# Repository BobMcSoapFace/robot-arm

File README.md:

# robot-arm

robot-arm is a 4-axis robot arm designed with modularity in mind. Depending on the maximum torque output of the motors and maximum range of the I2C wires, this project can support numerous limbs with only minor changes in code. Currently, the code is fixed to allowing two limbs and a hand on the robot.

I built this project mostly to challenge myself to tackle more complicated electronic and mechanical designs, but also because most hobbyist robot arms focus on using claws or grippers to pick up objects. For this project, the minor change of a claw to a hand that can sense its own orientation as well as high gear ratios allows for supporting heavier objects such as displays and light fixtures. 

All materials can be found within BOM.csv.
# Electronics
## Limb Controller PCB

## Main Controller PCB

# Setup Instructions
## Electronics
First solder the components onto each board based on the diagrams above. For this project only 1 of the main controller boards are required, however 5 limb controller boards are required as well (with 1 not requiring a corresponding stepper motor nor driver).

On the main controller board, use PlatformIO to flash the main controller board using the code in /code/MainController. Since the board runs on an ESP32, flashing using other tools is likely be supported. Do not connect the XT60 while simultaneously flashing.

On the limb controller boards, use PlatformIO to flash via USB-C. While USB-C is connected, hold down the BOOT0 button and press the NRST button to enter DFU mode. Adjust the two parameters listed in the program based on which gearBox the controller is intended to be used for. Then, flash the firmware in /code/LimbController. 

## Assembly
Unless specified otherwise, all screws mentioned in the steps below refer to M4 1.6cm long screws meant for M4x6x6 inserts.
### Step 1 - baseSunGear

| Object | Print Quantity |
| --- | --- |
| 1 | 1x1 |
| 2 | 1x1 |
\* The "xN" represents the total number of gearboxes that require this part (meaning that a 3x4 quantity will need to be printed 12 times total)
1. For every hole about 0.7cm in diameter in every printable part, insert a M4x6x6 heat set threaded insert. 
   * In this part, only 1 threaded insert is required (the attachment between part 1 and part 2)
2. Screw part 1 to part 2.
3. Repeat this process 3 more times, for a total baseSunGear quantity of 4.
### Step 2 - gearReducer

<ins>**Note: There is a baseSunGear supposed to be between parts 1 and 2 and the three gears, but is hidden for better clarity.**</ins>
| Object | Print Quantity |
| --- | --- |
| 1 | 1x4 |
| 2 | 1x4 |
| 3 | 1x4 |
| 4 | 1x4 |
| Gear (27 teeth) | 3x4 |
\* The "xN" represents the total number of gearboxes that require this part (meaning that a 3x4 quantity will need to be printed 12 times total)

1. For every hole about 0.7cm in diameter in every printable part, insert a M4x6x6 heat set threaded insert. 
2. Using a hammer or other means, press fit a 6907ZZ bearing into part 1.
3. For each of the three 27 tooth gears, press fit a 6805 bearing into its cavity.
4. With the smaller hole side facing upwards, place each of the 3 gears on the poles of part 1.
5. Press fit a 6907ZZ bearing into the center hole of part 2.
6. With the baseSunGear's circular side of its part 2, press fit the baseSunGear into the 6907ZZ bearing of part 1 (the baseSunGear protruding upwards and aligning its teeth with the three gears).
7. Press fit part 2's 6907ZZ bearing on the baseSunGear's part 1.
7. Screw part 2 to part 1.
8. Screw part 3 to part 2.
9. Screw part 4 to part 3.
10. Repeat this process 3 more times, for a total gearReducer quantity of 4.
### Step 3 - gearReducerOutput

| Object | Print Quantity |
| --- | --- |
| 1 | 1x4 |
| 2 | 1x4 |
| 3 | 1x4 |
| Gear (27 teeth) | 3x4 |
\* The "xN" represents the total number of gearboxes that require this part (meaning that a 3x4 quantity will need to be printed 12 times total)
1. For every hole about 0.7cm in diameter in every printable part, insert a M4x6x6 heat set threaded insert. 
2. Using a hammer or other means, press fit a 6907ZZ bearing into part 1.
3. For each of the three 27 tooth gears, press fit a 6805 bearing into its cavity.
4. With the smaller hole side facing upwards, place each of the 3 gears on the poles of part 1.
5. Press fit a 6907ZZ bearing into the center hole of part 2.
6. Screw part 2 to part 1.
7. Screw part 3 to part 2.
9. Repeat this process 3 more times, for a total gearReducerOutput quantity of 4.
### Step 4 - gearBox

<ins>**Note: There is a 6020 bearing supposed to be between parts 1 and 2, but is hidden for better clarity.**</ins>
| Object | Print Quantity |
| --- | --- |
| 1 | 1x4 |
| 2 | 1x4 |
| 3 | 1x4 |
| 4 | 1x4 |
| 5 | 1x4 |
| 6 | 2x4 |
| gearReducerOutput | 1x4 |
| gearReducer | 1x4 |
| baseSunGear | 1x4 |
| Nema17 Stepper Motor | 1x4 |

1. For every hole about 0.7cm in diameter in every printable part, insert a M4x6x6 heat set threaded insert. 
2. Screw the two part 6's together using the outer brackets.
3. Screw the joined part 6's to part 7.
4. Screw part 4 to part 7.
5. Screw part 5 to part 7, with the screw terminals being accessible from the provided holes.
6. Align the asymmetrical shaft of the Nema17 stepper motor to the gearReducer's baseSunGear corresponding hole of the same shape, attaching the two objects.
7. Lower the gearReducer with the Nema17 into the ring gears, with the Nema17 aligning with the cavity provided by part 4.
8. Once the Nema17 is inside the cavity, screw part 3 to part 4, blocking the Nema17 from falling through.
9. Unscrew part 4 from part 3 for the gearReducer, and unscrew parts 2 and 3 from gearReducerOutput's part 1.
10. Lower the gearReducerOutput into the ring gear, aligning the 27 teeth gears with the base gear in the middle.
11. Screw back part 4 to part 3 for the gearReducer
12. Press fit the gearReducer's part 4 with the 6907ZZ bearing of the deattached gearReducerOutput's part 2, then screw parts 2 and 3 back to gearReducerOutput's part 1.
13. Press fit a 6020 bearing onto the gearbox's part 1, then press fit the bearing onto the gearReducerOutput's output cylinder (marked part 2)
14. Repeat 3 more times, for a total of 4 gearboxes.
### Step 5 - limb

| Object | Print Quantity |
| --- | --- |
| 1 | 1x2 |
| 3 | 2x2 |
| 4 | 1x2 |
| 5 | 1x2 |
| 7 | 1x2 |
| 8 | 1x2 |
| 9 | 1x2 |
| 10 | 1x2 |
| 11 | 1x2 |
| 12 | 1x2 |
| 13 | 1x2 |
| 14 | 1x2 |
\*Note that parts 15 and 6 are the same parts as 14 and 5 respectively.
1. For every hole about 0.7cm in diameter in every printable part, insert a M4x6x6 heat set threaded insert. 
2. On a gearbox, screw part 8 to the side with the controller.
3. Press fit a 6020 bearing to part 7, then screw part 7 to part 8.
4. Press fit part 1 to the bearing.
5. On the side of the gearbox outputting rotation, screw part 11 to the gearbox's output.
6. Screw part 12 to part 11.
7. Screw part 13 to parts 12 and 2.
8. Screw the two part 3's to part 13.
9. Screw part 5 to the two part 3's.
10. Screw part 4 to the part 3 on the side of the gearbox's controller.
11. Screw part 14 to the part 3 on the side of the gearbox's output.
12. Screw parts 14 and 4 to a second gearbox.
13. Repeat the steps above for a second limb, using the newly attached gearbox as the base (used in steps 2 and 5).
### Step 6 - base

| Object | Print Quantity |
| --- | --- |
| 1 | 1x1 |
| 2 | 7x1 |
| 4 | 1x1 |
| 5 | 7x1 |
| 6 | 8x1 |
| 7 | 1x1 |
| 8 | 1x1 |
| 9 | 1x1 |

\*Note that parts 15 and 6 are the same parts as 14 and 5 respectively.
1. For every hole about 0.7cm in diameter in every printable part, insert a M4x6x6 heat set threaded insert.
2. Using the inserts indicated by the region labeled #3, screw in 7 part 2's, avoiding the area covered by the gearbox controller.
3. To increase arm stability during movement, insert a heavy filler (e.g sand or gravel) or other similar heavy objects in equal distribution among the part 2's.
4. Screw a part 5 to each of the part 2's (7 total).
5. Screw a main controller PCB to part 1
6. Screw part 1 to the gearbox, and then screw part 7 to part 1.
7. Screw 8 part 6's to connect each of the part 7's together. 
7. With a gearbox in the middle and output side facing upwards, screw part 4 to the gearbox using the three holes.
### Step 7 - hand

| Object | Print Quantity |
| --- | --- |
| 1 | 1x1 |
| 2 | 1x1 |
| 3 | 1x1 |

1. For every hole about 0.7cm in diameter in every printable part, insert a M4x6x6 heat set threaded insert.
2. Screw part 3 to the output of the last limb's gearbox output.
3. Press fit a 6020 bearing to the last limb's gearbox controller side on the attached part, then press fit part 1 into the bearing.
4. Screw parts 1 and 3 together with part 2.
5. Screw the limb controller (part 4) to part 2.
   * Note that on this controller, an A4988 motor driver is not required.
### Step 8 - Connecting Limbs to Base
1. Using the screw terminals on each board, connect wires from the main controller to the limb controller in the base on one side. On the other side of the limb controller's screw terminals, connect more wires to the next gearbox's limb controllers, repeating the process for each controller until the hand's controller is connected.
   * You may have to unscrew some parts connecting to the gearbox to be able to reach the screw terminals.
   * Low capacitance wires are preferred, ex. solid core
   * Each terminal in the screw terminals on the limb controller are connected directly to the parallel terminal on the other screw terminal; simply connect the same terminals with each other
2. Lower the side of the first limb's initial gearbox with the output side facing the base's part 4 side with two holes for screws.
3. Deattach the limb's part 11 from the gearbox and part 12, then secure the gearbox in the base's part 4 by screwing in the two holes. Reattach part 11 afterwards.
4. On the other side of the gearbox, secure the gearbox with the three screw holes on base 4.

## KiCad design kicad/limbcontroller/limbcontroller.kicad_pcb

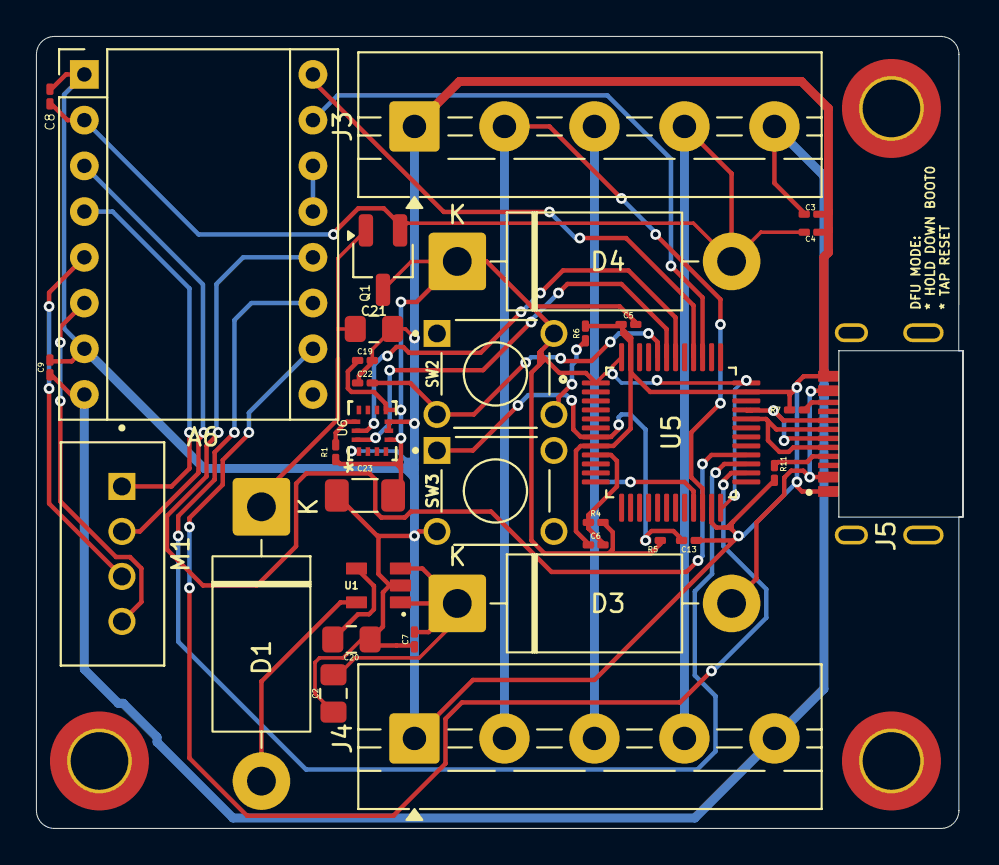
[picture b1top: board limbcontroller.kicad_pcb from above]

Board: 2 copper layers, 51.5 x 44.0 mm, 34 parts (0 on the bottom side), 32 nets.

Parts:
A6: Pololu_Breakout_A4988; Pololu_Breakout-16_15.2x20.3mm
C2, C21: 1uF; C_0805_2012Metric_Pad1.18x1.45mm_HandSolder
C3, C4, C5, C6, C8, C9, C13, C19, C22: 0.1uF; C_0201_0603Metric_Pad0.64x0.40mm_HandSolder
C7: 10uF; C_0201_0603Metric_Pad0.64x0.40mm_HandSolder
C20: 22uF; C_0805_2012Metric_Pad1.18x1.45mm_HandSolder
C23: 0.01uF; C_1206_3216Metric_Pad1.33x1.80mm_HandSolder
D1, D3, D4: 1N5821; D_DO-201AD_P15.24mm_Horizontal
J3, J4: Screw_Terminal_01x05; TerminalBlock_MaiXu_MX126-5.0-05P_1x05_P5.00mm
J5: USB_C_Receptacle_USB2.0_14P; 2340901-1
M1: Stepper_Motor_bipolar; JST_B4B-XH-A
Q1: DTB143EK
R1: 100kΩ; R_0201_0603Metric_Pad0.64x0.40mm_HandSolder
R4: 470Ω; R_0201_0603Metric_Pad0.64x0.40mm_HandSolder
R5, R6: 10kΩ; R_0201_0603Metric_Pad0.64x0.40mm_HandSolder
R7, R11: 5.1kΩ; R_0201_0603Metric_Pad0.64x0.40mm_HandSolder
SW2, SW3: 1825910-6; SW_1825910-6-4
U1: RT9193-33GB; RT9193-SOT94P279X129-5N
U5: STM32F103C8T6; STM32F103-QFP50P900X900X160-48N
U6: BMI323; BMI323_BOS

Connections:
+3.3V: C5.2, C22.2, C23.2, D4.1 (K), Q1.C, R1.1, R4.1, R5.1, SW2.2, U5.1 (VBAT), U5.24 (VDD), U5.36 (VDD), U5.48 (VDD), U6.5 (VDDIO), U6.8 (VDD)
/VCC: A6.2 (VDD), C4.1, C8.1, D4.2 (A), J3.4, J4.4, Q1.B
/VMOT: A6.8 (VMOT), C3.1, C9.2, J3.5, J4.5
D+: J5.A6 (D+), J5.B6 (D+), U5.33 (PA12)
D-: J5.A7 (D-), J5.B7 (D-), U5.32 (PA11)
DIR: A6.16 (DIR), U5.40 (PB4)
GND: A6.1 (GND), A6.7 (GND), C2.1, C3.2, C4.2, C5.1, C6.1, C7.1, C8.2, C9.1, C13.1, C19.1, C20.1, C21.1, C22.1, C23.1, J3.1, J4.1, J5.A1/B12 (GND), J5.B1/A12 (GND), R6.2, R7.2, R11.1, SW3.3, U1.2 (GND), U5.8 (VSSA), U5.23 (VSS), U5.35 (VSS), U5.47 (VSS), U6.1 (SDO), U6.6 (GNDIO), U6.7 (GND)
MS1: A6.10 (MS1), U5.26 (PB13)
MS2: A6.11 (MS2), U5.27 (PB14)
MS3: A6.12 (MS3), U5.28 (PB15)
unnamed: A6.4 (1A), M1.1
unnamed: A6.3 (1B), M1.2 (-_2)
unnamed: A6.5 (2A), M1.3
unnamed: A6.6 (2B), M1.4
unnamed: A6.13 (~RESET), A6.14 (~SLEEP)
unnamed: D1.2 (A), U1.5 (VOUT)
unnamed: C21.2, D1.1 (K), Q1.E
unnamed: D3.2 (A), J5.A4/B9 (VBUS), J5.B4/AP (VBUS)
unnamed: C2.2, C7.2, D3.1 (K), U1.1 (VIN), U1.3 (EN)
unnamed: J5.A5 (CC1), R11.2
unnamed: J5.B5 (CC2), R7.1
unnamed: R6.1, SW2.4
unnamed: C20.2, U1.4 (BP)
unnamed: C19.2, SW2.3, U5.44 (BOOT0)
unnamed: C13.2, R5.2, SW3.1, U5.7 (NRST)
unnamed: C6.2, R4.2, U5.9 (VDDA)
unnamed: R1.2, U6.12 (CSB)
SCL: J3.3, J4.3, U5.21 (PB10)
SCL2: U5.42 (PB6), U6.13 (SCX)
SDA: J3.2, J4.2, U5.22 (PB11)
SDA2: U5.43 (PB7), U6.14 (SDX)
STEP: A6.15 (STEP), U5.39 (PB3)

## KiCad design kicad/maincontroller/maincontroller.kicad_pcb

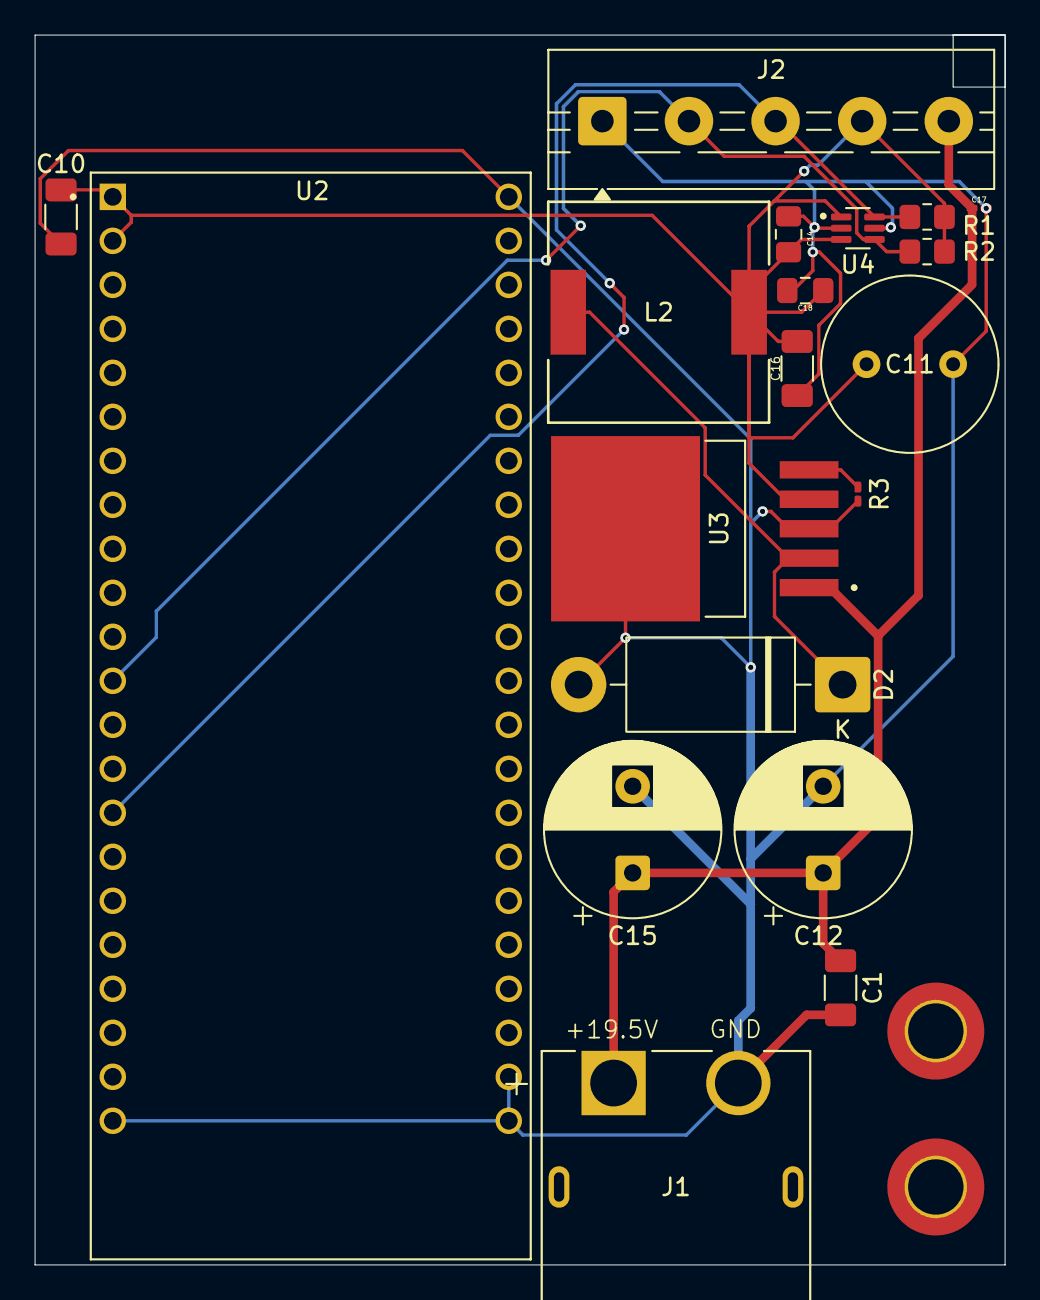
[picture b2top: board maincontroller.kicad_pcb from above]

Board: 2 copper layers, 56.0 x 71.0 mm, 19 parts (0 on the bottom side), 7 nets.

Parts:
C1, C10, C16: 0.01uF; C_1206_3216Metric_Pad1.33x1.80mm_HandSolder
C11: 220uF; C_Radial_D10.0mm_H20.0mm_P5.00mm
C12, C15: 680uF; CP_Radial_D10.0mm_P5.00mm
C14, C18: 1uF; C_0805_2012Metric_Pad1.18x1.45mm_HandSolder
C17: 10uF; C_0201_0603Metric_Pad0.64x0.40mm_HandSolder
D2: 1N5821; D_DO-201AD_P15.24mm_Horizontal
J1: XT60PW-M; AMASS_XT60PW-M
J2: Screw_Terminal_01x05; TerminalBlock_MaiXu_MX126-5.0-05P_1x05_P5.00mm
L2: 33uH; IND_DR127-330-R_EAT
R1, R2: 4kΩ; R_0805_2012Metric_Pad1.20x1.40mm_HandSolder
R3: 10kΩ; R_0201_0603Metric_Pad0.64x0.40mm_HandSolder
U2: ESP32-S3-DEVKITC-1-N8R2; XCVR_ESP32-S3-DEVKITC-1-N8R2
U3: LM2596S-3.3_NOPB; VREG_LM2596S-3.3_NOPB
U4: LTC4311ISC6_TRPBF; LTC4311-SOT65P210X100-6N

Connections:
+3.3V: C10.1, C11.1, C14.1, C16.1, C18.1, J2.4, L2.2, R1.1, R2.1, U2.J1_1 (3V3), U2.J1_2 (3V3), U3.4 (FB), U4.1 (VCC), U4.3 (ENABLE)
+19.5V: C1.1, C12.1, C15.1, C17.1, J1.1, J2.5, U3.1 (VIN)
GND: C1.2, C10.2, C11.2, C12.2, C14.2, C15.2, C16.2, C17.2, C18.2, D2.2 (A), J1.2 (N), J2.1, R3.2, U2.J1_22 (GND), U2.J3_1 (GND), U2.J3_21 (GND), U2.J3_22 (GND), U3.3 (GND), U3.6 (GND), U4.2 (GND), U4.5 (GND)
unnamed: D2.1 (K), L2.1, U3.2 (OUT)
unnamed: R3.1, U3.5 (~ON/OFF)
SCL: J2.3, R1.2, U2.J1_15 (GPIO9), U4.6 (BUS1)
SDA: J2.2, R2.2, U2.J1_12 (GPIO8), U4.4 (BUS2)

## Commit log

2026-06-06 added project README.md
2026-06-07 added CAD model images and files
2026-06-07 added pcb gerber files
2026-06-07 cleaned up kicad files and changed 1uf capacitors to 0805 SMD size
2026-06-07 added baseSunGear printables & diagram
2026-06-08 updated project README.md and fixed main controller code
2026-06-09 added zine
2026-06-09 fixed readme
2026-06-09 clarified wiring in readme
2026-06-09 fixed missing B4B-XH-A in BOM
